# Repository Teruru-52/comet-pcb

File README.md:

# comet-pcb
Micromouse

## v1.0
<div style="text-align: center;">
    
</div>

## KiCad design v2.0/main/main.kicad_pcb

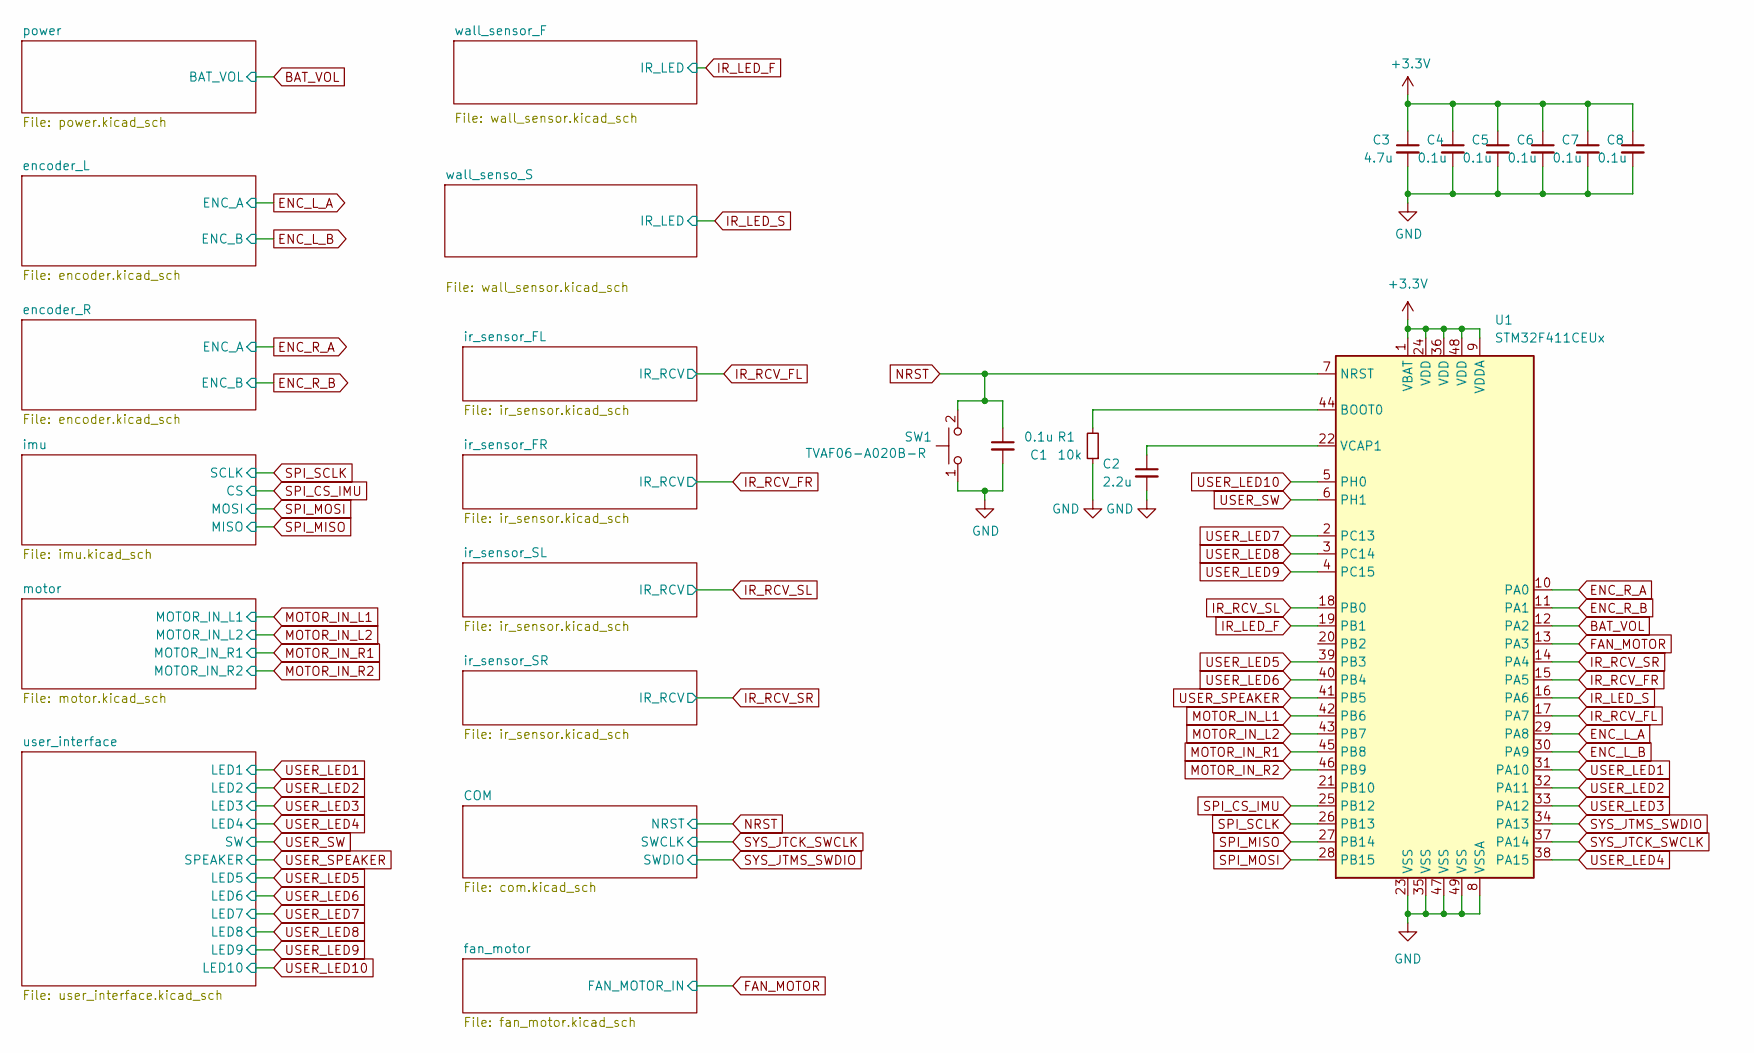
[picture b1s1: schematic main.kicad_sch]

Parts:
C1, C4, C5, C6, C7, C8: 0.1u; C_0201_0603Metric
C2: 2.2u; C_0402_1005Metric
C3: 4.7u; C_0402_1005Metric
R1: 10k; R_0201_0603Metric
SW1: TVAF06-A020B-R
U1: STM32F411CEUx; QFN-48-1EP_7x7mm_P0.5mm_EP5.6x5.6mm

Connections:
+3.3V: C3.1, C4.1, C5.1, C6.1, C7.1, C8.1, U1.1 (VBAT), U1.9 (VDDA), U1.24 (VDD), U1.36 (VDD), U1.48 (VDD); also elsewhere on the board
BAT_VOL: U1.12 (PA2); also elsewhere on the board
ENC_L_A: U1.29 (PA8); also elsewhere on the board
ENC_L_B: U1.30 (PA9); also elsewhere on the board
ENC_R_A: U1.10 (PA0); also elsewhere on the board
ENC_R_B: U1.11 (PA1); also elsewhere on the board
FAN_MOTOR: U1.13 (PA3); also elsewhere on the board
GND: C1.2, C2.2, C3.2, C4.2, C5.2, C6.2, C7.2, C8.2, R1.1, SW1.1, U1.8 (VSSA), U1.23 (VSS), U1.35 (VSS), U1.47 (VSS), U1.49 (VSS); also elsewhere on the board
IR_LED_F: U1.19 (PB1); also elsewhere on the board
IR_LED_S: U1.16 (PA6); also elsewhere on the board
IR_RCV_FL: U1.17 (PA7); also elsewhere on the board
IR_RCV_FR: U1.15 (PA5); also elsewhere on the board
IR_RCV_SL: U1.18 (PB0); also elsewhere on the board
IR_RCV_SR: U1.14 (PA4); also elsewhere on the board
MOTOR_IN_L1: U1.42 (PB6); also elsewhere on the board
MOTOR_IN_L2: U1.43 (PB7); also elsewhere on the board
MOTOR_IN_R1: U1.45 (PB8); also elsewhere on the board
MOTOR_IN_R2: U1.46 (PB9); also elsewhere on the board
NRST: C1.1, SW1.2, U1.7 (NRST); also elsewhere on the board
unnamed: R1.2, U1.44 (BOOT0)
unnamed: C2.1, U1.22 (VCAP1)
SPI_CS_IMU: U1.25 (PB12); also elsewhere on the board
SPI_MISO: U1.27 (PB14); also elsewhere on the board
SPI_MOSI: U1.28 (PB15); also elsewhere on the board
SPI_SCLK: U1.26 (PB13); also elsewhere on the board
SYS_JTCK_SWCLK: U1.37 (PA14); also elsewhere on the board
SYS_JTMS_SWDIO: U1.34 (PA13); also elsewhere on the board
USER_LED1: U1.31 (PA10); also elsewhere on the board
USER_LED2: U1.32 (PA11); also elsewhere on the board
USER_LED3: U1.33 (PA12); also elsewhere on the board
USER_LED4: U1.38 (PA15); also elsewhere on the board
USER_LED5: U1.39 (PB3); also elsewhere on the board
USER_LED6: U1.40 (PB4); also elsewhere on the board
USER_LED7: U1.2 (PC13); also elsewhere on the board
USER_LED8: U1.3 (PC14); also elsewhere on the board
USER_LED9: U1.4 (PC15); also elsewhere on the board
USER_LED10: U1.5 (PH0); also elsewhere on the board
USER_SPEAKER: U1.41 (PB5); also elsewhere on the board
USER_SW: U1.6 (PH1); also elsewhere on the board

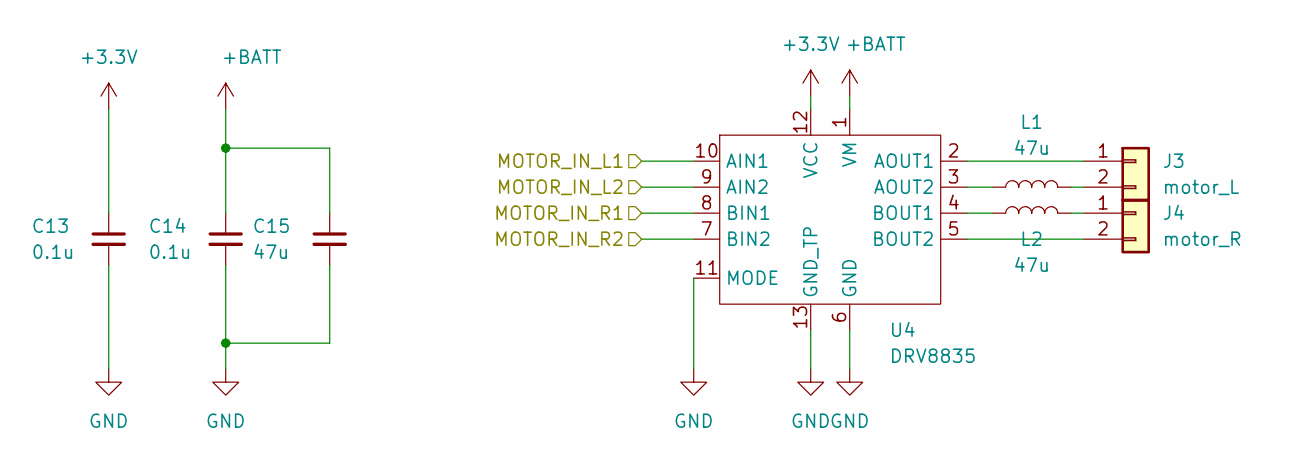
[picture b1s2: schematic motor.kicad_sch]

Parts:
C13, C14: 0.1u; C_0201_0603Metric
C15: 47u; C_0603_1608Metric
J3: motor_L; PinHeader_1x02_P1.00mm_Vertical
J4: motor_R; PinHeader_1x02_P1.00mm_Vertical
L1, L2: 47u; L_0603_1608Metric_Pad1.05x0.95mm_HandSolder
U4: DRV8835

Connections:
+3.3V: C13.1, U4.12 (VCC); also elsewhere on the board
+BATT: C14.1, C15.1, U4.1 (VM); also elsewhere on the board
GND: C13.2, C14.2, C15.2, U4.6 (GND), U4.11 (MODE), U4.13 (GND_TP); also elsewhere on the board
MOTOR_IN_L1: U4.10 (AIN1); also elsewhere on the board
MOTOR_IN_L2: U4.9 (AIN2); also elsewhere on the board
MOTOR_IN_R1: U4.8 (BIN1); also elsewhere on the board
MOTOR_IN_R2: U4.7 (BIN2); also elsewhere on the board
unnamed: J3.1, U4.2 (AOUT1)
unnamed: J3.2, L1.2
unnamed: J4.1, L2.2
unnamed: J4.2, U4.5 (BOUT2)
unnamed: L1.1, U4.3 (AOUT2)
unnamed: L2.1, U4.4 (BOUT1)

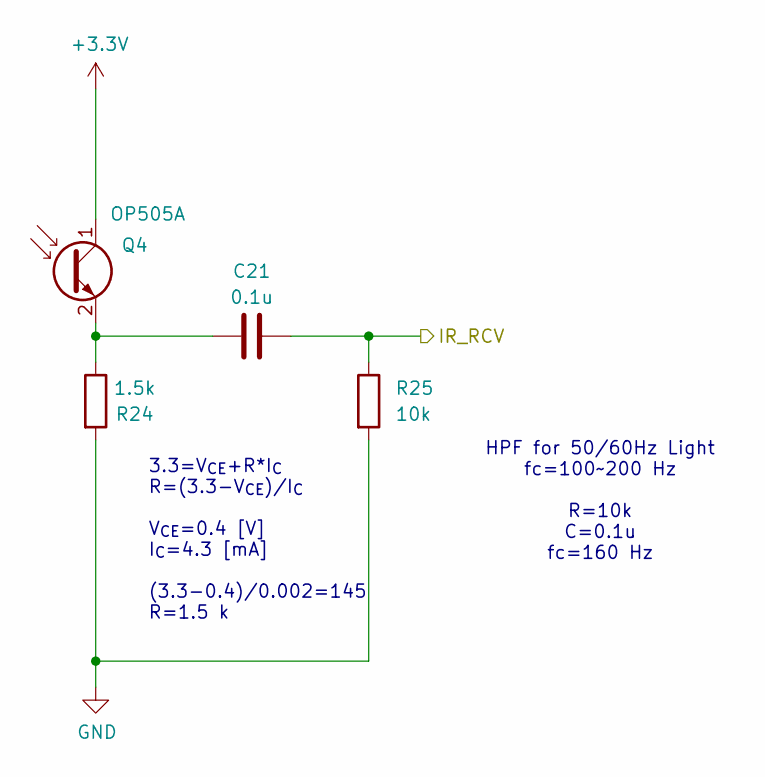
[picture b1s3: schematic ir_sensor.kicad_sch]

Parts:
C21: 0.1u; C_0402_1005Metric
Q4: OP505A; LTR-209
R24: 1.5k; R_0402_1005Metric
R25: 10k; R_0402_1005Metric

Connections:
+3.3V: Q4.1 (C); also elsewhere on the board
GND: R24.2, R25.2; also elsewhere on the board
IR_RCV_FR: C21.1, R25.1; also elsewhere on the board
unnamed: C21.2, Q4.2 (E), R24.1

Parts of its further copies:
C16, C22, C23: 0.1u; C_0402_1005Metric
Q1, Q5, Q6: OP505A; LTR-209
R4, R26, R28: 1.5k; R_0402_1005Metric
R5, R27, R29: 10k; R_0402_1005Metric

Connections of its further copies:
+3.3V: Q1.1 (C), Q5.1 (C), Q6.1 (C); also elsewhere on the board
GND: R4.2, R5.2, R26.2, R27.2, R28.2, R29.2; also elsewhere on the board
IR_RCV_FL: C16.1, R5.1; also elsewhere on the board
IR_RCV_SL: C22.1, R27.1; also elsewhere on the board
IR_RCV_SR: C23.1, R29.1; also elsewhere on the board
unnamed: C16.2, Q1.2 (E), R4.1
unnamed: C22.2, Q5.2 (E), R26.1
unnamed: C23.2, Q6.2 (E), R28.1

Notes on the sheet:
HPF for 50/60Hz Light fc=100~200 Hz R=10k C=0.1u fc=160 Hz
3.3=V_{CE}+R*I_{C} R=(3.3-V_{CE})/I_{C} V_{CE}=0.4 [V] I_{C}=4.3 [mA] (3.3-0.4)/0.002=145 R=1.5 k

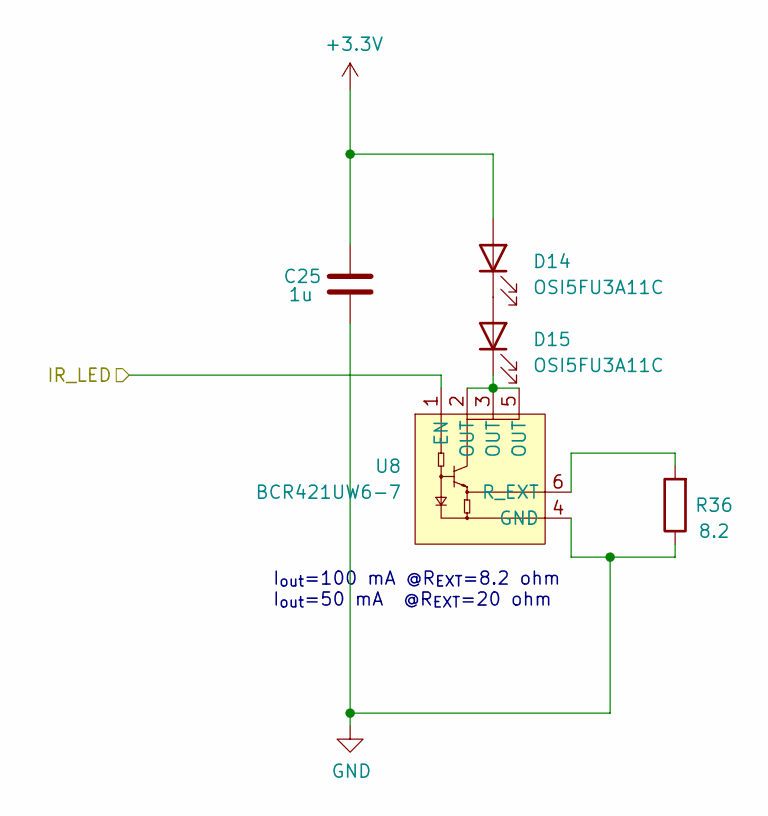
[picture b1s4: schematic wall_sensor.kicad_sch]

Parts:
C25: 1u; C_0402_1005Metric
D14, D15: OSI5FU3A11C
R36: 8.2; R_0402_1005Metric
U8: BCR421UW6-7; SOT-23-6

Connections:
+3.3V: C25.1, D14.2 (A); also elsewhere on the board
GND: C25.2, R36.1, U8.4 (GND); also elsewhere on the board
IR_LED_F: U8.1 (EN); also elsewhere on the board
unnamed: D14.1 (K), D15.2 (A)
unnamed: D15.1 (K), U8.2 (OUT), U8.3 (OUT), U8.5 (OUT)
unnamed: R36.2, U8.6 (R_EXT)

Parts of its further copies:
C24: 1u; C_0402_1005Metric
D12, D13: OSI5FU3A11C
R35: 8.2; R_0402_1005Metric
U7: BCR421UW6-7; SOT-23-6

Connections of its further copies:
+3.3V: C24.1, D12.2 (A); also elsewhere on the board
GND: C24.2, R35.1, U7.4 (GND); also elsewhere on the board
IR_LED_S: U7.1 (EN); also elsewhere on the board
unnamed: D12.1 (K), D13.2 (A)
unnamed: D13.1 (K), U7.2 (OUT), U7.3 (OUT), U7.5 (OUT)
unnamed: R35.2, U7.6 (R_EXT)

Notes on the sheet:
I_{out}=100 mA @R_{EXT}=8.2 ohm I_{out}=50 mA @R_{EXT}=20 ohm

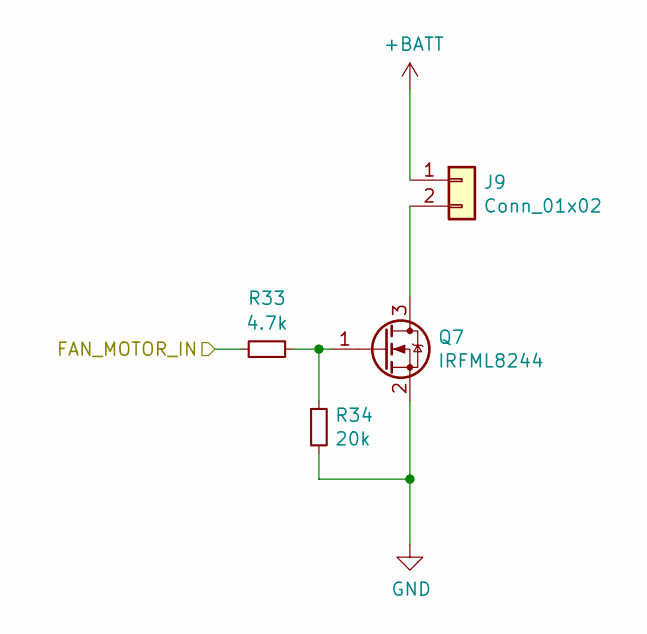
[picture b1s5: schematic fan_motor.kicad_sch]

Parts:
J9: Conn_01x02; PinHeader_1x02_P1.00mm_Vertical
Q7: IRFML8244; SOT-23
R33: 4.7k; R_0201_0603Metric
R34: 20k; R_0201_0603Metric

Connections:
+BATT: J9.1; also elsewhere on the board
FAN_MOTOR: R33.1; also elsewhere on the board
GND: Q7.2, R34.2; also elsewhere on the board
unnamed: J9.2, Q7.3
unnamed: Q7.1, R33.2, R34.1

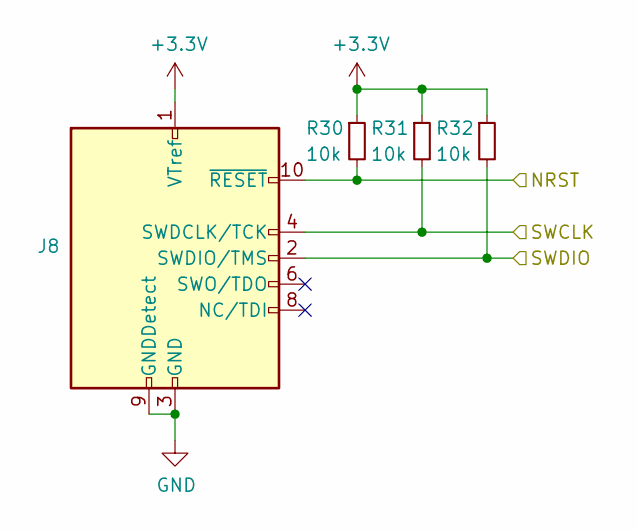
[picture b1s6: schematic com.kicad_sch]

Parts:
J8: Conn_ARM_JTAG_SWD_10; PinHeader_2x05_P1.27mm_Vertical
R30, R31, R32: 10k; R_0201_0603Metric

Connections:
+3.3V: J8.1 (VTref), R30.1, R31.1, R32.1; also elsewhere on the board
GND: J8.3 (GND), J8.5 (GND), J8.9 (GNDDetect); also elsewhere on the board
NRST: J8.10 (~RESET), R30.2; also elsewhere on the board
SYS_JTCK_SWCLK: J8.4 (SWDCLK/TCK), R31.2; also elsewhere on the board
SYS_JTMS_SWDIO: J8.2 (SWDIO/TMS), R32.2; also elsewhere on the board

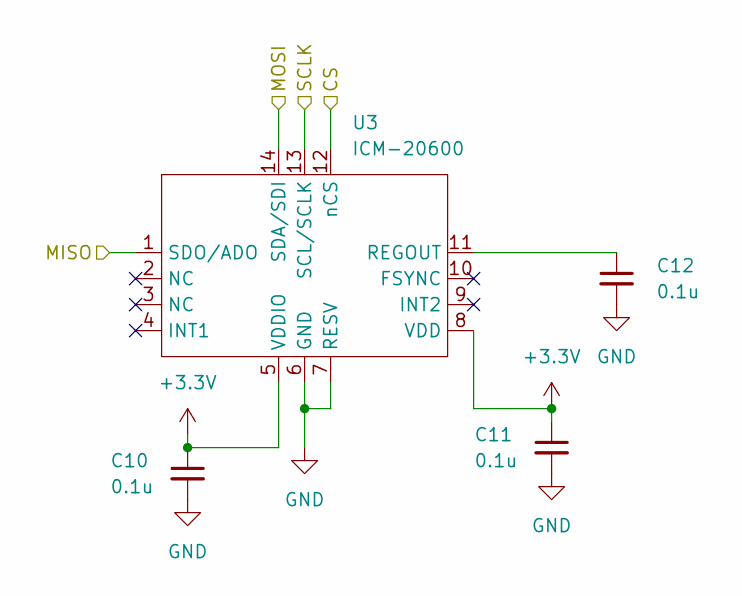
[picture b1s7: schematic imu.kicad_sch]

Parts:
C10, C11, C12: 0.1u; C_0201_0603Metric
U3: ICM-20600; LGA-14_3x2.5mm_P0.5mm_LayoutBorder3x4y

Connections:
+3.3V: C10.1, C11.1, U3.5 (VDDIO), U3.8 (VDD); also elsewhere on the board
GND: C10.2, C11.2, C12.2, U3.6 (GND), U3.7 (RESV); also elsewhere on the board
unnamed: C12.1, U3.11 (REGOUT)
SPI_CS_IMU: U3.12 (nCS); also elsewhere on the board
SPI_MISO: U3.1 (SDO/ADO); also elsewhere on the board
SPI_MOSI: U3.14 (SDA/SDI); also elsewhere on the board
SPI_SCLK: U3.13 (SCL/SCLK); also elsewhere on the board

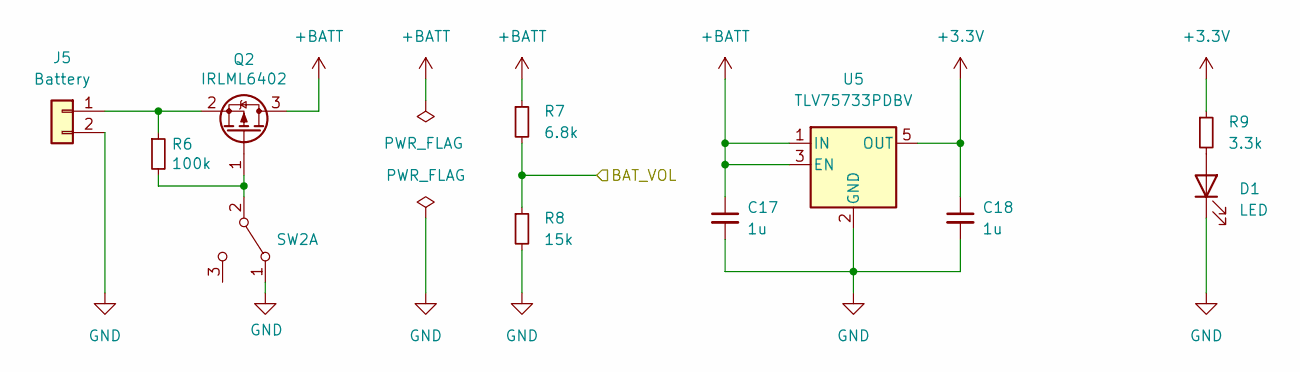
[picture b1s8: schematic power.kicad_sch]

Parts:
C17, C18: 1u; C_0402_1005Metric
D1: LED; LED_0402_1005Metric
J5: Battery; PinSocket_1x02_P1.27mm_Vertical
Q2: IRLML6402; SOT-23
R6: 100k; R_0201_0603Metric
R7: 6.8k; R_0201_0603Metric
R8: 15k; R_0402_1005Metric
R9: 3.3k; R_0201_0603Metric
SW2: EG1215AA
U5: TLV75733PDBV; SOT-23-5

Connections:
+3.3V: C18.1, R9.1, U5.5 (OUT); also elsewhere on the board
+BATT: C17.1, Q2.3 (D), R7.1, U5.1 (IN), U5.3 (EN); also elsewhere on the board
BAT_VOL: R7.2, R8.1; also elsewhere on the board
GND: C17.2, C18.2, D1.1 (K), J5.2, R8.2, SW2.1 (A), U5.2 (GND); also elsewhere on the board
unnamed: D1.2 (A), R9.2
unnamed: J5.1, Q2.2 (S), R6.1
unnamed: Q2.1 (G), R6.2, SW2.2 (B)

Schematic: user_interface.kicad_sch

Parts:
C20: 0.1u; C_0201_0603Metric
D2: LED1; LED_0402_1005Metric
D3: LED2; LED_0402_1005Metric
D4: LED3; LED_0402_1005Metric
D5: LED4; LED_0402_1005Metric
D6: LED5; LED_0402_1005Metric
D7: LED6; LED_0402_1005Metric
D8: LED7; LED_0402_1005Metric
D9: LED8; LED_0402_1005Metric
D10: LED9; LED_0402_1005Metric
D11: LED10; LED_0402_1005Metric
Q3: BSS138; SOT-23
R12, R13, R14, R15, R16, R17, R18, R19, R20, R21: 3.3k; R_0201_0603Metric
R22: 10k; R_0201_0603Metric
R23: 100k; R_0201_0603Metric
SP1: SMT-0440; SMT-0440-T-HT-R
SW3: TVAF06-A020B-R

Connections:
+3.3V: R22.1, SP1.1; also elsewhere on the board
GND: C20.2, D2.1 (K), D3.1 (K), D4.1 (K), D5.1 (K), D6.1 (K), D7.1 (K), D8.1 (K), D9.1 (K), D10.1 (K), D11.1 (K), Q3.2 (S), R23.2, SW3.1; also elsewhere on the board
unnamed: D2.2 (A), R12.2
unnamed: D3.2 (A), R13.2
unnamed: D4.2 (A), R14.2
unnamed: D5.2 (A), R15.2
unnamed: D6.2 (A), R16.2
unnamed: D7.2 (A), R17.2
unnamed: D8.2 (A), R18.2
unnamed: D9.2 (A), R19.2
unnamed: D10.2 (A), R20.2
unnamed: D11.2 (A), R21.2
unnamed: Q3.3 (D), SP1.2
USER_LED1: R12.1; also elsewhere on the board
USER_LED2: R13.1; also elsewhere on the board
USER_LED3: R14.1; also elsewhere on the board
USER_LED4: R15.1; also elsewhere on the board
USER_LED5: R16.1; also elsewhere on the board
USER_LED6: R17.1; also elsewhere on the board
USER_LED7: R18.1; also elsewhere on the board
USER_LED8: R19.1; also elsewhere on the board
USER_LED9: R20.1; also elsewhere on the board
USER_LED10: R21.1; also elsewhere on the board
USER_SPEAKER: Q3.1 (G), R23.1; also elsewhere on the board
USER_SW: C20.1, R22.2, SW3.2; also elsewhere on the board

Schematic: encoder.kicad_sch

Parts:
C19: 0.1u; C_0201_0603Metric
J6: enc_host; enc_fp
J7: enc_slave; enc_board
R10, R11: 10k; R_0201_0603Metric
U6: MA730; QFN-16-1EP_3x3mm_P0.5mm_EP1.75x1.75mm

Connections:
+3.3V: J6.1; also elsewhere on the board
/encoder_L/ENC_A_: J7.2, U6.2 (A)
/encoder_L/ENC_B_: J7.3, U6.6 (B)
/encoder_L/s_GND: C19.2, J7.1, R10.1, R11.1, U6.8 (GND), U6.10 (TEST), U6.17 (PAD)
/encoder_L/s_VDD: C19.1, J7.4, U6.13 (VDD)
ENC_L_A: J6.3; also elsewhere on the board
ENC_L_B: J6.2; also elsewhere on the board
GND: J6.4; also elsewhere on the board
unnamed: R11.2, U6.16 (MGH)
unnamed: R10.2, U6.11 (MGL)

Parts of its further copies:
C9: 0.1u; C_0201_0603Metric
J1: enc_host; enc_fp
J2: enc_slave; enc_board
R2, R3: 10k; R_0201_0603Metric
U2: MA730; QFN-16-1EP_3x3mm_P0.5mm_EP1.75x1.75mm

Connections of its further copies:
+3.3V: J1.1; also elsewhere on the board
/encoder_R/ENC_A_: J2.2, U2.2 (A)
/encoder_R/ENC_B_: J2.3, U2.6 (B)
/encoder_R/s_GND: C9.2, J2.1, R2.1, R3.1, U2.8 (GND), U2.10 (TEST), U2.17 (PAD)
/encoder_R/s_VDD: C9.1, J2.4, U2.13 (VDD)
ENC_R_A: J1.3; also elsewhere on the board
ENC_R_B: J1.2; also elsewhere on the board
GND: J1.4; also elsewhere on the board
unnamed: R3.2, U2.16 (MGH)
unnamed: R2.2, U2.11 (MGL)

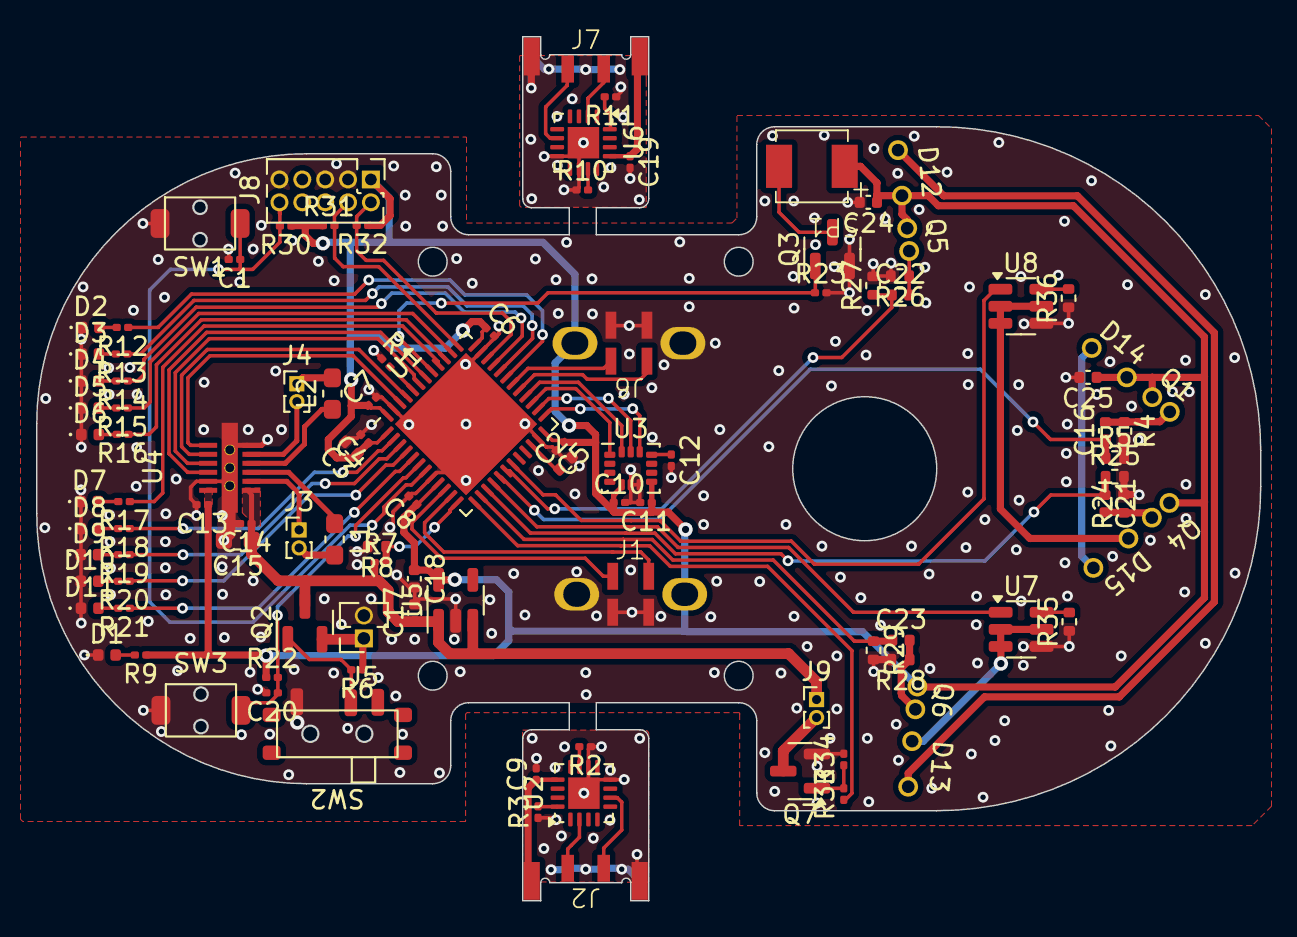
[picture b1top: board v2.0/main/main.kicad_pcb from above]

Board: 2 copper layers, 68.0 x 48.0 mm, 106 parts (0 on the bottom side), 85 nets.

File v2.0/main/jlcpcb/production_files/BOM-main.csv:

Comment,Designator,Footprint,LCSC,Quantity
20k,R34,R_0201_0603Metric,C105575,1
100k,"R23,R6",R_0201_0603Metric,C106224,2
ICM-20600,U3,LGA-14_3x2.5mm_P0.5mm_LayoutBorder3x4y,C124140,1
DRV8835,U4,DRV8835,C129328,1
0.1u,"C16,C21,C22,C23",C_0402_1005Metric,C133086,4
4.7k,R33,R_0201_0603Metric,C138135,1
IRFML8244,Q7,SOT-23,C143945,1
1u,"C17,C18,C24,C25",C_0402_1005Metric,C14445,4
15k,R8,R_0402_1005Metric,C144795,1
0.1u,"C1,C10,C11,C12,C13,C14,C19,C20,C4,C5,C6,C7,C8,C9",C_0201_0603Metric,C160831,14
MA730,"U2,U6",QFN-16-1EP_3x3mm_P0.5mm_EP1.75x1.75mm,C161798,2
BCR421UW6-7,"U7,U8",SOT-23-6,C194382,2
47u,"L1,L2",L_0603_1608Metric_Pad1.05x0.95mm_HandSolder,C223165,2
4.7u,C3,C_0402_1005Metric,C23733,1
10k,"R1,R10,R11,R2,R22,R3,R30,R31,R32",R_0201_0603Metric,C2479090,9
IRLML6402,Q2,SOT-23,C2593,1
3.3k,"R12,R13,R14,R15,R16,R17,R18,R19,R20,R21,R9",R_0201_0603Metric,C274874,11
6.8k,R7,R_0201_0603Metric,C274877,1
1.5k,"R24,R26,R28,R4",R_0402_1005Metric,C281775,4
LED10,"D11,D6",LED_0402_1005Metric,C2852592,2
LED,"D1,D3,D8",LED_0402_1005Metric,C2853065,3
8.2,"R35,R36",R_0402_1005Metric,C309552,2
SMT-0440,SP1,SMT-0440-T-HT-R,C3812225,1
47u,C15,C_0603_1608Metric,C3848273,1
TLV75733PDBV,U5,SOT-23-5,C485517,1
2.2u,C2,C_0402_1005Metric,C521077,1
BSS138,Q3,SOT-23,C52895,1
LED3,"D4,D9",LED_0402_1005Metric,C5875733,2
LED9,"D10,D5",LED_0402_1005Metric,C5875753,2
STM32F411CEUx,U1,QFN-48-1EP_7x7mm_P0.5mm_EP5.6x5.6mm,C60420,1
10k,"R25,R27,R29,R5",R_0402_1005Metric,C60489,4
TVAF06-A020B-R,SW1,TVAF06-A020B-R,,1
OSI5FU3A11C,D12,OSI5FU3A11C,,1
OSI5FU3A11C,D14,OSI5FU3A11C,,1
LED6,D7,LED_0402_1005Metric,,1
OSI5FU3A11C,D15,OSI5FU3A11C,,1
OP505A,Q1,LTR-209,,1
OSI5FU3A11C,D13,OSI5FU3A11C,,1
EG1215AA,SW2,EG1215AA,,1
LED1,D2,LED_0402_1005Metric,,1
enc_slave,J2,enc_board,,1
Conn_ARM_JTAG_SWD_10,J8,PinHeader_2x05_P1.27mm_Vertical,,1
OP505A,Q4,LTR-209,,1
OP505A,Q5,LTR-209,,1
Battery,J5,PinSocket_1x02_P1.27mm_Vertical,,1
Conn_01x02,J9,PinHeader_1x02_P1.00mm_Vertical,,1
OP505A,Q6,LTR-209,,1
motor_R,J4,PinHeader_1x02_P1.00mm_Vertical,,1
motor_L,J3,PinHeader_1x02_P1.00mm_Vertical,,1
TVAF06-A020B-R,SW3,TVAF06-A020B-R,,1
enc_host,J1,enc_fp,,1
enc_slave,J7,enc_board,,1
enc_host,J6,enc_fp,,1

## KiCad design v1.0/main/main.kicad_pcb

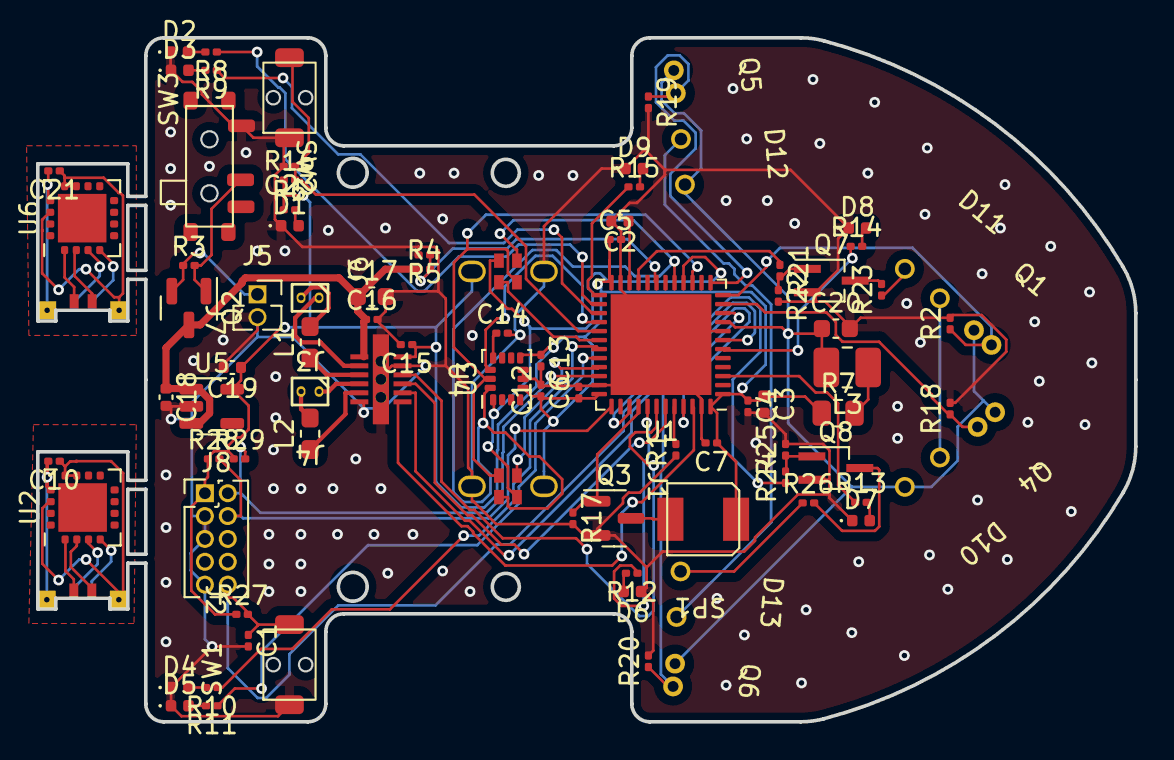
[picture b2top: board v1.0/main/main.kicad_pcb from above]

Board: 2 copper layers, 61.0 x 38.0 mm, 90 parts (0 on the bottom side), 76 nets.

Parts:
C1, C4, C5, C6, C7, C10, C12, C13, C14, C15, C16, C21, C23: 0.1u; C_0201_0603Metric
C2: 2.2u; C_0402_1005Metric
C3: 4.7u; C_0402_1005Metric
C17, C20: 47u; C_0603_1608Metric
C18, C19: 1u; C_0402_1005Metric
D1: LED; LED_0402_1005Metric
D2: LED1; LED_0402_1005Metric
D3: LED2; LED_0402_1005Metric
D4: LED3; LED_0402_1005Metric
D5: LED4; LED_0402_1005Metric
D6: LED5; LED_0402_1005Metric
D7: LED6; LED_0402_1005Metric
D8: LED7; LED_0402_1005Metric
D9: LED8; LED_0402_1005Metric
D10, D11, D12, D13: OSI5FU3A11C
J1, J6: enc_host; encoder_board_host
J2, J7: enc_slave; encoder_board
J3: motor_L; motor_SMD
J4: motor_R; motor_SMD
J5: Battery; PinSocket_1x02_P1.27mm_Vertical
J8: Conn_ARM_JTAG_SWD_10; PinHeader_2x05_P1.27mm_Vertical
L1, L2: 47u; L_0603_1608Metric_Pad1.05x0.95mm_HandSolder
L3: 10u; L_1008_2520Metric_Pad1.43x2.20mm_HandSolder
Q1, Q4, Q5, Q6: LTR-209
Q2: IRLML6402; SOT-23
Q3: BSS138; SOT-23
Q7, Q8: PMF250XNEX; SOT-323_SC-70_Handsoldering
R1, R2, R4, R5, R16, R18, R19, R20, R27, R28, R29: 10k; R_0201_0603Metric
R3, R17: 100k; R_0201_0603Metric
R6, R8, R9, R10, R11, R12, R13, R14, R15, R21, R22, R24, R25: 1k; R_0201_0603Metric
R7: 5; R_0805_2012Metric
R23, R26: 5.6; R_0201_0603Metric
SP1: SMT-0440; STM0440-T-R
SW1, SW3: TVAF06-A020B-R
SW2: EG1215AA
U1: STM32F411CEUx; QFN-48-1EP_7x7mm_P0.5mm_EP5.6x5.6mm
U2, U6: AS5055A; QFN-16-1EP_4x4mm_P0.65mm_EP2.7x2.7mm_PullBack
U3: ICM-20600; LGA-14_3x2.5mm_P0.5mm_LayoutBorder3x4y
U4: DRV8835
U5: TLV75733PDBV; SOT-23-5

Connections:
+3.3V: C3.1, C4.1, C5.1, C6.1, C7.1, C12.1, C13.1, C15.1, C19.1, J1.1, J6.1, J8.1 (VTref), R6.1, R7.1, R16.1, R27.1, R28.1, R29.1, SP1.1, U1.1 (VBAT), U1.24 (VDD), U1.36 (VDD), U1.48 (VDD), U3.5 (VDDIO), U3.8 (VDD), U4.12 (VCC), U5.5 (OUT)
+3.3VADC: C20.1, D10.2 (A), D12.2 (A), L3.2, Q1.1 (C), Q4.1 (C), Q5.1 (C), Q6.1 (C), U1.9 (VDDA)
+BATT: C16.1, C17.1, C18.1, Q2.3 (D), R4.1, U4.1 (VM), U5.1 (IN), U5.3 (EN)
/encoder_L/s_CS: J7.4, U6.4 (~SS)
/encoder_L/s_GND: C21.2, J7.6, U6.13 (VSS)
/encoder_L/s_MISO: J7.2, U6.2 (MISO)
/encoder_L/s_MOSI: J7.3, U6.1 (MOSI)
/encoder_L/s_SCK: J7.5, U6.3 (SCK)
/encoder_L/s_VDD: C21.1, J7.1, U6.11 (VDDp), U6.12 (VDD), U6.14 (WM)
/encoder_R/s_CS: J2.4, U2.4 (~SS)
/encoder_R/s_GND: C10.2, J2.6, U2.13 (VSS)
/encoder_R/s_MISO: J2.2, U2.2 (MISO)
/encoder_R/s_MOSI: J2.3, U2.1 (MOSI)
/encoder_R/s_SCK: J2.5, U2.3 (SCK)
/encoder_R/s_VDD: C10.1, J2.1, U2.11 (VDDp), U2.12 (VDD), U2.14 (WM)
BAT_VOL: R4.2, R5.1, U1.19 (PB1)
GND: C1.2, C2.2, C3.2, C4.2, C5.2, C6.2, C7.2, C12.2, C13.2, C14.2, C15.2, C16.2, C17.2, C18.2, C19.2, C20.2, C23.2, D1.1 (K), D2.1 (K), D3.1 (K), D4.1 (K), D5.1 (K), D6.1 (K), D7.1 (K), D8.1 (K), D9.1 (K), J1.6, J5.2, J6.6, J8.3 (GND), J8.5 (GND), J8.9 (GNDDetect), Q3.2 (S), Q7.2 (S), Q8.2 (S), R1.1, R2.2, R5.2, R17.2, R18.2, R19.2, R20.2, R22.2, R25.2, SW1.1, SW2.1 (A), SW3.1, U1.8 (VSSA), U1.23 (VSS), U1.35 (VSS), U1.47 (VSS), U1.49 (VSS), U3.6 (GND), U3.7 (RESV), U4.6 (GND), U4.11 (MODE), U4.13 (GND_TP), U5.2 (GND)
IR_LED_F: R21.1, U1.21 (PB10)
IR_LED_S: R24.1, U1.39 (PB3)
IR_RCV_FL: Q1.2 (E), R2.1, U1.12 (PA2)
IR_RCV_FR: Q4.2 (E), R18.1, U1.11 (PA1)
IR_RCV_SL: Q5.2 (E), R19.1, U1.13 (PA3)
IR_RCV_SR: Q6.2 (E), R20.1, U1.10 (PA0)
MOTOR_IN_L1: U1.42 (PB6), U4.10 (AIN1)
MOTOR_IN_L2: U1.43 (PB7), U4.9 (AIN2)
MOTOR_IN_R1: U1.45 (PB8), U4.8 (BIN1)
MOTOR_IN_R2: U1.46 (PB9), U4.7 (BIN2)
NRST: C1.1, J8.10 (~RESET), R27.2, SW1.2, U1.7 (NRST)
unnamed: C2.1, U1.22 (VCAP1)
unnamed: C14.1, U3.11 (REGOUT)
unnamed: D1.2 (A), R6.2
unnamed: D2.2 (A), R8.2
unnamed: D3.2 (A), R9.2
unnamed: D4.2 (A), R10.2
unnamed: D5.2 (A), R11.2
unnamed: D6.2 (A), R12.2
unnamed: D7.2 (A), R13.2
unnamed: D8.2 (A), R14.2
unnamed: D9.2 (A), R15.2
unnamed: D10.1 (K), D11.2 (A)
unnamed: D11.1 (K), R23.1
unnamed: D12.1 (K), D13.2 (A)
unnamed: D13.1 (K), R26.1
unnamed: J3.1, U4.2 (AOUT1)
unnamed: J3.2, L1.2
unnamed: J4.1, U4.4 (BOUT1)
unnamed: J4.2, L2.2
unnamed: J5.1, Q2.2 (S), R3.1
unnamed: L1.1, U4.3 (AOUT2)
unnamed: L2.1, U4.5 (BOUT2)
unnamed: L3.1, R7.2
unnamed: Q2.1 (G), R3.2, SW2.2 (B)
unnamed: Q3.3 (D), SP1.2
unnamed: Q7.1 (G), R21.2, R22.1
unnamed: Q7.3 (D), R23.2
unnamed: Q8.1 (G), R24.2, R25.1
unnamed: Q8.3 (D), R26.2
unnamed: R1.2, U1.44 (BOOT0)
SPI_CS_ENC_L: J6.4, U1.30 (PA9)
SPI_CS_ENC_R: J1.4, U1.33 (PA12)
SPI_CS_IMU: U1.28 (PB15), U3.12 (nCS)
SPI_MISO: J1.2, J6.2, U1.16 (PA6), U3.1 (SDO/ADO)
SPI_MOSI: J1.3, J6.3, U1.17 (PA7), U3.14 (SDA/SDI)
SPI_SCLK: J1.5, J6.5, U1.15 (PA5), U3.13 (SCL/SCLK)
SYS_JTCK_SWCLK: J8.4 (SWDCLK/TCK), R28.2, U1.37 (PA14)
SYS_JTMS_SWDIO: J8.2 (SWDIO/TMS), R29.2, U1.34 (PA13)
USER_LED1: R8.1, U1.26 (PB13)
USER_LED2: R9.1, U1.27 (PB14)
USER_LED3: R10.1, U1.31 (PA10)
USER_LED4: R11.1, U1.32 (PA11)
USER_LED5: R12.1, U1.41 (PB5)
USER_LED6: R13.1, U1.3 (PC14)
USER_LED7: R14.1, U1.6 (PH1)
USER_LED8: R15.1, U1.25 (PB12)
USER_SPEAKER: Q3.1 (G), R17.1, U1.40 (PB4)
USER_SW: C23.1, R16.2, SW3.2, U1.29 (PA8)

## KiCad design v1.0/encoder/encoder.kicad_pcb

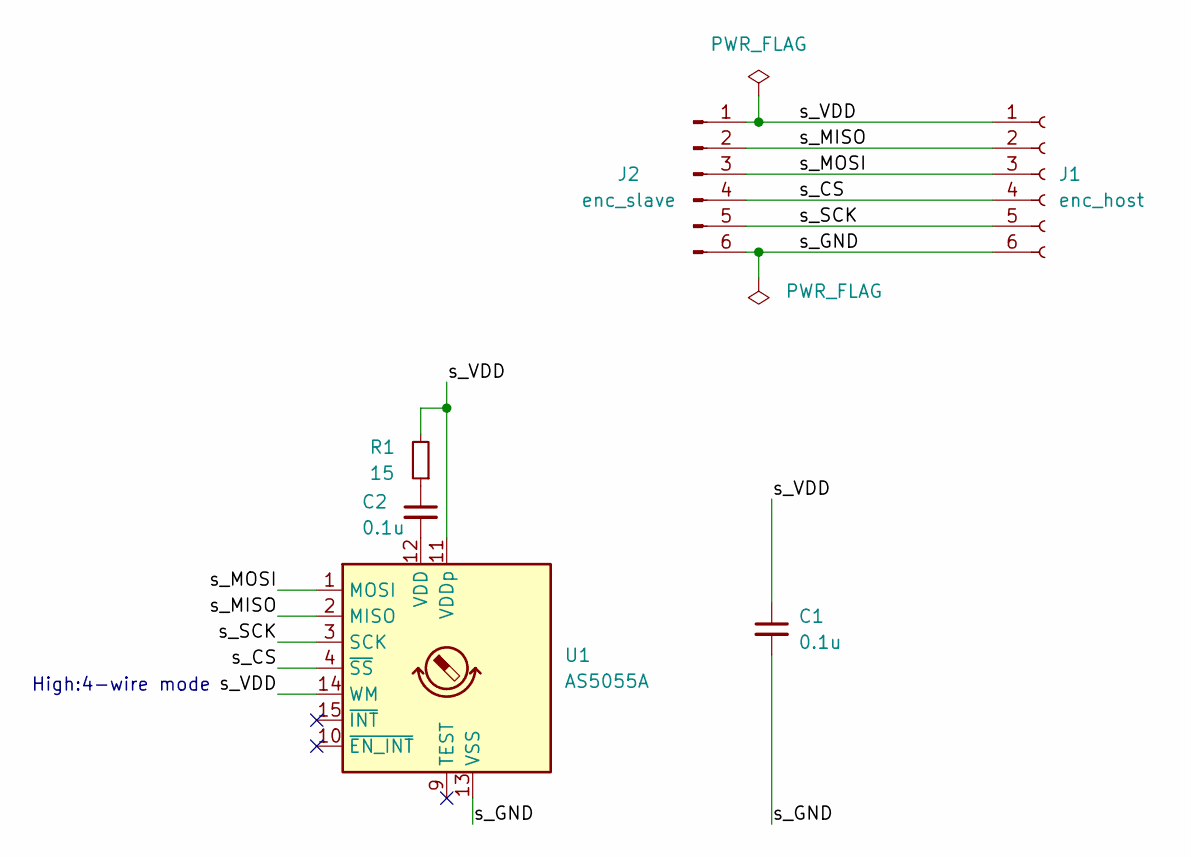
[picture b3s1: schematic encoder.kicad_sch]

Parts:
C1, C2: 0.1u; C_0201_0603Metric
J1: enc_host; PinSocket_1x06_P1.27mm_Vertical
J2: enc_slave; encoder_board
R1: 15; R_0201_0603Metric
U1: AS5055A; QFN-16-1EP_4x4mm_P0.65mm_EP2.7x2.7mm_PullBack

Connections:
/s_CS: J1.4, J2.4, U1.4 (~SS)
/s_GND: C1.2, J1.6, J2.6, U1.13 (VSS)
/s_MISO: J1.2, J2.2, U1.2 (MISO)
/s_MOSI: J1.3, J2.3, U1.1 (MOSI)
/s_SCK: J1.5, J2.5, U1.3 (SCK)
/s_VDD: C1.1, J1.1, J2.1, R1.2, U1.11 (VDDp), U1.14 (WM)
unnamed: C2.1, R1.1
unnamed: C2.2, U1.12 (VDD)

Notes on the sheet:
High:4-wire mode

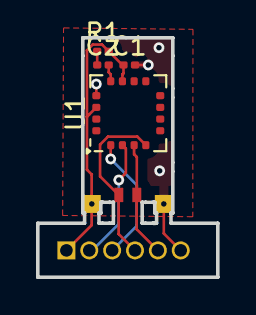
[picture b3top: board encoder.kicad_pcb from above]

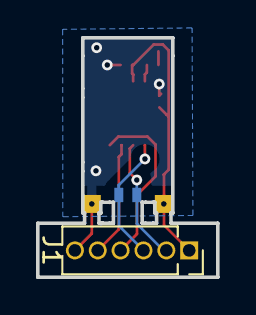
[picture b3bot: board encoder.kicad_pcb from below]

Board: 2 copper layers, 10.0 x 13.3 mm, 6 parts (2 on the bottom side), 8 nets.

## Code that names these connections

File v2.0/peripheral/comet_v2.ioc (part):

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Mcu.Name=STM32F411C(C-E)Ux
Mcu.Package=UFQFPN48
Mcu.UserName=STM32F411CEUx
PA0-WKUP.Signal=S_TIM5_CH1
PA1.Signal=S_TIM5_CH2
PA10.GPIOParameters=GPIO_Label
PA10.GPIO_Label=LED3
PA10.Signal=GPIO_Output
PA11.GPIOParameters=GPIO_Label
PA11.GPIO_Label=LED4
PA11.Signal=GPIO_Output
PA12.GPIOParameters=GPIO_Label
PA12.GPIO_Label=SW
PA12.Signal=GPIO_Input
PA13.Mode=Serial_Wire
PA13.Signal=SYS_JTMS-SWDIO
PA14.Mode=Serial_Wire
PA14.Signal=SYS_JTCK-SWCLK
PA15.GPIOParameters=GPIO_Label
PA15.GPIO_Label=LED5
PA15.Signal=GPIO_Output
PA2.Signal=ADCx_IN2
PA3.Signal=S_TIM9_CH2
PA4.Signal=ADCx_IN4
PA5.Signal=ADCx_IN5
PA6.Signal=S_TIM3_CH1
PA7.Signal=ADCx_IN7
PA8.Signal=S_TIM1_CH1
PA9.Signal=S_TIM1_CH2
PB0.Signal=ADCx_IN8
PB1.Signal=S_TIM3_CH4
PB10.GPIOParameters=GPIO_Label
PB10.GPIO_Label=LED2
PB10.Signal=GPIO_Output
PB12.GPIOParameters=GPIO_Label
PB12.GPIO_Label=SPI2_CS_IMU
PB12.Signal=GPIO_Output
PB13.Mode=Full_Duplex_Master
PB13.Signal=SPI2_SCK
PB14.Mode=Full_Duplex_Master
PB14.Signal=SPI2_MISO
PB15.Mode=Full_Duplex_Master
PB15.Signal=SPI2_MOSI
PB2.GPIOParameters=GPIO_Label
PB2.GPIO_Label=LED1
PB2.Signal=GPIO_Output
PB3.GPIOParameters=GPIO_Label
PB3.GPIO_Label=LED6
PB3.Signal=GPIO_Output
PB4.GPIOParameters=GPIO_Label
PB4.GPIO_Label=LED7
PB4.Signal=GPIO_Output
PB5.Signal=S_TIM3_CH2
PB6.Signal=S_TIM4_CH1
PB7.Signal=S_TIM4_CH2
PB8.Signal=S_TIM4_CH3
PB9.Signal=S_TIM4_CH4
PC13-ANTI_TAMP.GPIOParameters=GPIO_Label
PC13-ANTI_TAMP.GPIO_Label=LED8
PC13-ANTI_TAMP.Signal=GPIO_Output
PC14-OSC32_IN.GPIOParameters=GPIO_Label
PC14-OSC32_IN.GPIO_Label=LED9
PC14-OSC32_IN.Signal=GPIO_Output
PC15-OSC32_OUT.GPIOParameters=GPIO_Label
PC15-OSC32_OUT.GPIO_Label=LED10
PC15-OSC32_OUT.Signal=GPIO_Output
RCC.HSE_VALUE=16000000
RCC.SYSCLKFreq_VALUE=96000000
RCC.SYSCLKSource=RCC_SYSCLKSOURCE_PLLCLK
board=custom

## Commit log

2023-05-27 placement complete
2025-02-25 feat: update main board
2025-02-25 feat: update encoder board
2025-02-25 refactor: rename dxf files
2025-02-25 refactor: remove backups
2025-02-25 refactor: directory structure
2025-02-25 chore: update readme
2025-02-25 chore: update .gitignore
2025-02-25 chore: add v2.0 files
2025-02-25 perf: add library for comet
2025-02-25 perf: add dxf
2025-02-25 perf: remove old library
2025-02-25 feat: update pcb routing
2025-02-25 feat: add vias
2025-02-26 fix: parts position
2025-02-26 fix: encoder position
2025-02-26 fix: DRC errors
2025-02-26 chore: add dxf
2025-02-26 refactor: remove encoder files
2025-02-27 feat: order to JLCPCB
